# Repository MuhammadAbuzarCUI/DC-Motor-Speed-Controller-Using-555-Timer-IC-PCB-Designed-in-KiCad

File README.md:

# DC-Motor-Speed-Controller-Using-555-Timer-IC-PCB-Designed-in-KiCad
PCB design of a DC motor speed controller using the 555 timer IC to generate a PWM signal for speed control. Includes circuit schematic and PCB layout for motor speed regulation by adjusting the PWM duty cycle.

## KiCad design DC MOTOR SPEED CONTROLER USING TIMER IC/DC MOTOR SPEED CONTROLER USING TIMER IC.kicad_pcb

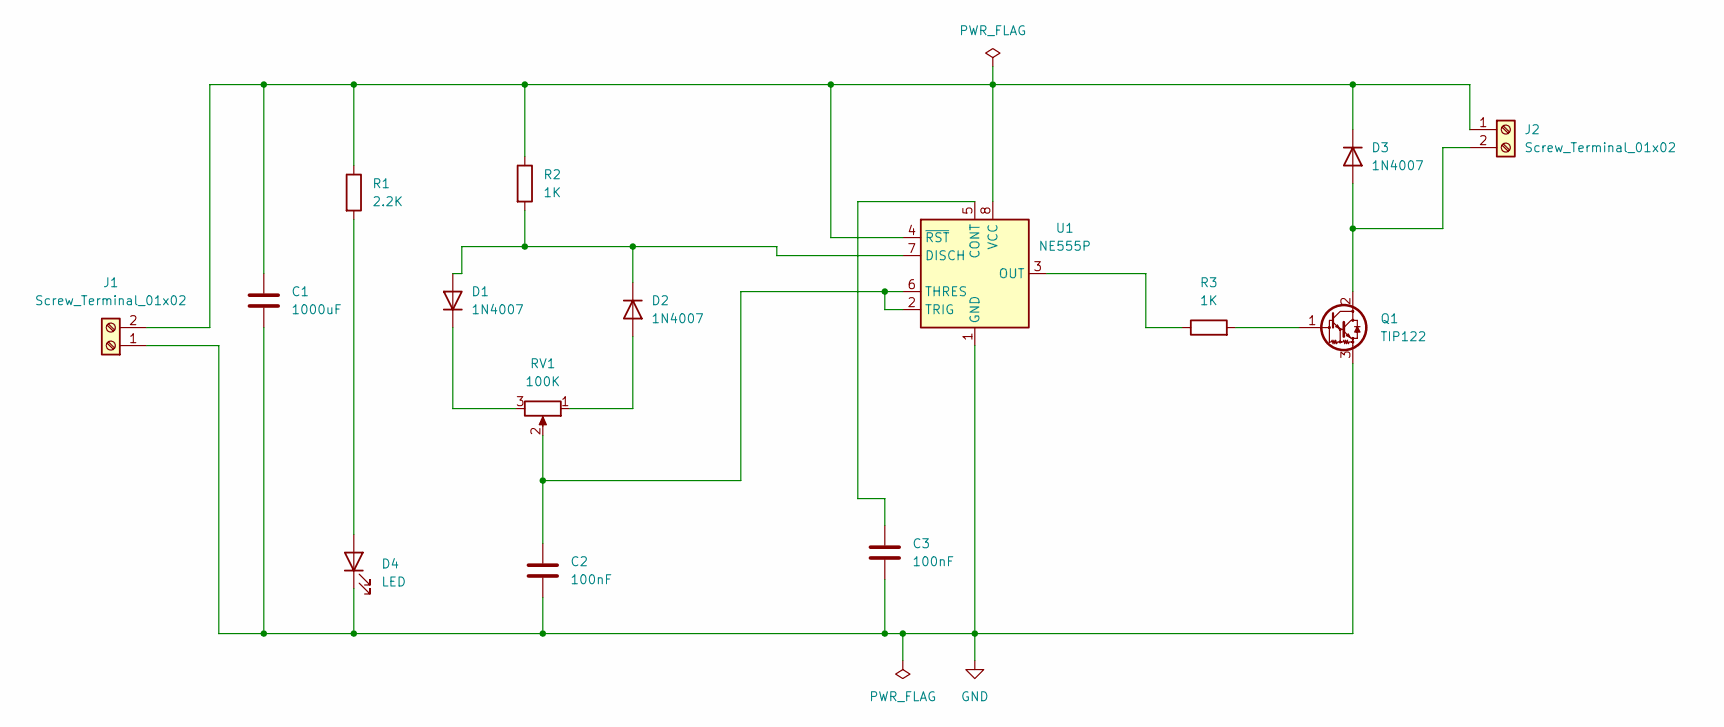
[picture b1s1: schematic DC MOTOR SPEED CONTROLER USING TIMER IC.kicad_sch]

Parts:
C1: 1000uF; CP_Radial_D10.0mm_P5.00mm
C2, C3: 100nF; C_Disc_D4.7mm_W2.5mm_P5.00mm
D1, D2, D3: 1N4007; D_DO-41_SOD81_P10.16mm_Horizontal
D4: LED; LED_D5.0mm
J1, J2: Screw_Terminal_01x02; TerminalBlock_MaiXu_MX126-5.0-02P_1x02_P5.00mm
Q1: TIP122; TO-220-3_Vertical
R1: 2.2K; R_Axial_DIN0204_L3.6mm_D1.6mm_P7.62mm_Horizontal
R2, R3: 1K; R_Axial_DIN0204_L3.6mm_D1.6mm_P7.62mm_Horizontal
RV1: 100K; Potentiometer_Alps_RK163_Single_Horizontal
U1: NE555P; DIP-8_W7.62mm

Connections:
GND: C1.2, C2.2, C3.2, D4.1 (K), J1.1, Q1.3 (E), U1.1 (GND)
unnamed: D1.2 (A), D2.1 (K), R2.2, U1.7 (DISCH)
unnamed: D1.1 (K), RV1.3
unnamed: D2.2 (A), RV1.1
unnamed: D3.2 (A), J2.2, Q1.2 (C)
unnamed: C1.1, D3.1 (K), J1.2, J2.1, R1.1, R2.1, U1.4 (~RST), U1.8 (VCC)
unnamed: D4.2 (A), R1.2
unnamed: Q1.1 (B), R3.2
unnamed: C3.1, U1.5 (CONT)
unnamed: R3.1, U1.3 (OUT)
unnamed: C2.1, RV1.2, U1.2 (TRIG), U1.6 (THRES)

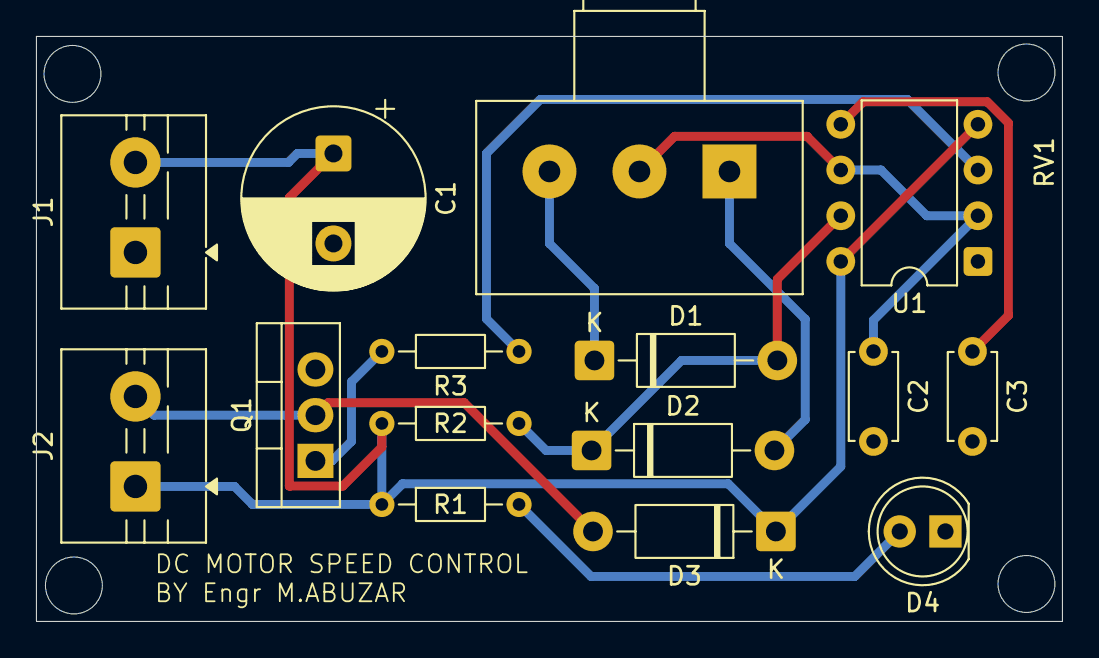
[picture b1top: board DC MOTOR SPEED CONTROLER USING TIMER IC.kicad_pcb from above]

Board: 2 copper layers, 57.0 x 32.5 mm, 15 parts (0 on the bottom side), 11 nets.
